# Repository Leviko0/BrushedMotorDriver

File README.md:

# BrushedMotorDriver

This driver board is designed for two 12V brushed motors based on an ESP32 and two DRV8245. It utilizes the NCV68261 for reverse current and reverse polarity protection and for power enable.

## Hardware overview

- **MCU:** ESP32-S3-WROOM-1
- **Motor drivers:** 2x TI DRV8245 (12V brushed DC motor driver)
- **Protection:** NCV68261 for reverse current/polarity protection and power enable, with DRVOFF fault handling
- **Power input:** XT60 connector for a 4S LiPo battery
- **Regulator:** TLV75533 LDO, 3.3V rail for the ESP32
- **Programming/data:** USB-C connector (USB 2.0)

## PCB design

- **4-layer stackup** with dedicated ground and power planes, to separate the ESP32's digital/RF signals from the motor drivers' switching noise
- **Thermal via arrays** under the DRV8245 exposed pads for heat dissipation
- **Ground stitching vias** to keep return paths low-impedance across the board
- **Trace widths scaled by current:** wider power traces for the motor outputs, standard-width traces for signal/logic

Schematic: <br />

<br />

PCB: <br />

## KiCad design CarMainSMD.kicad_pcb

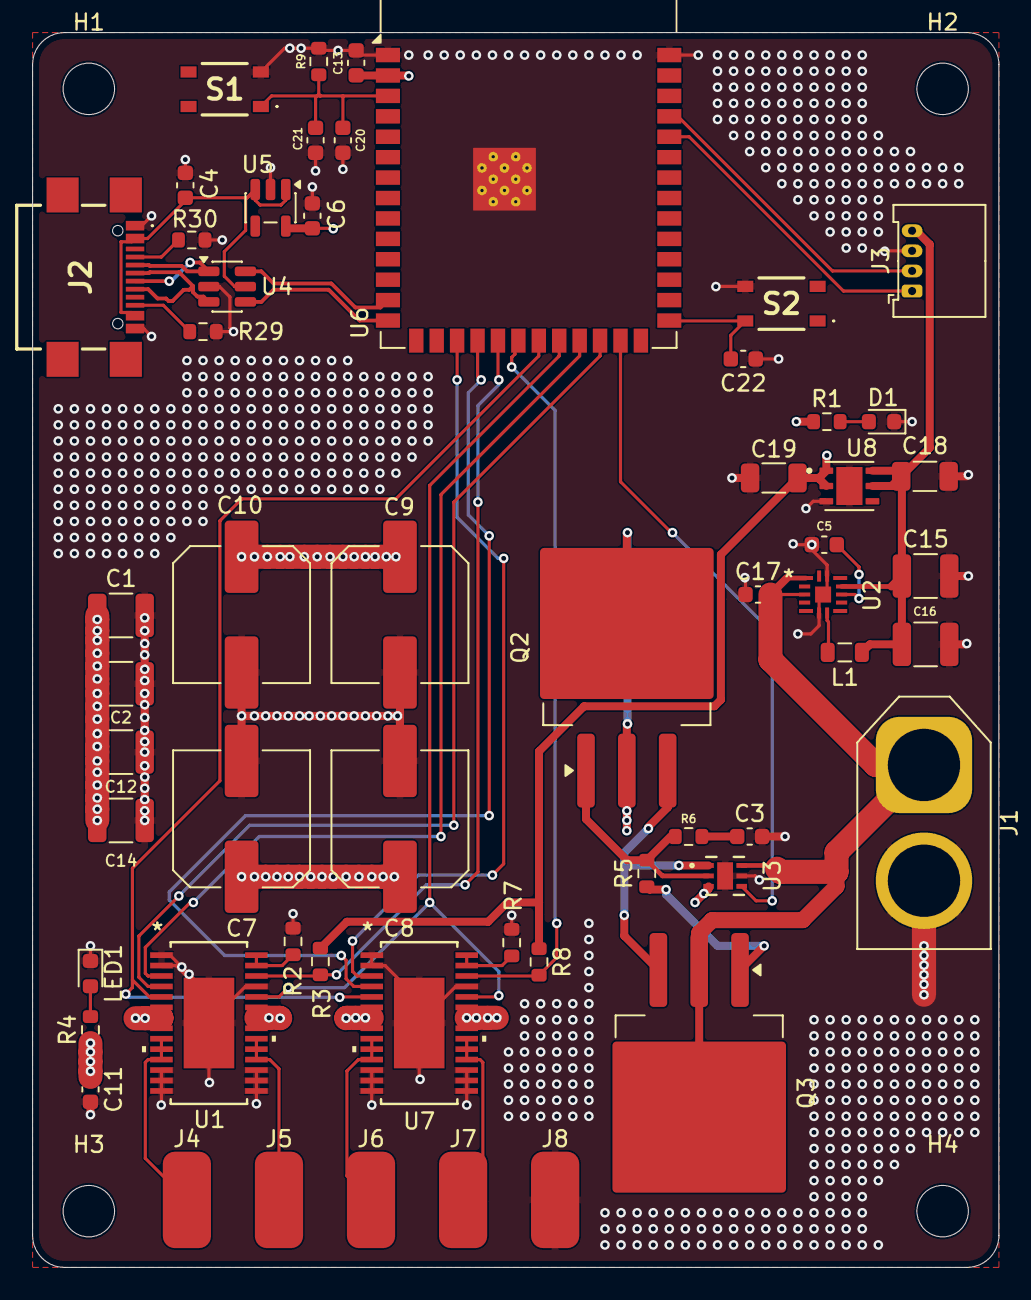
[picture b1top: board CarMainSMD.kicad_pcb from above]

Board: 4 copper layers, 60.1 x 76.8 mm, 60 parts (0 on the bottom side), 39 nets.

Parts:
C1, C2, C12, C14, C15, C16: 22uF; C_1210_3225Metric
C3: 20nF; C_0603_1608Metric
C4, C5, C21: 1uF; C_0603_1608Metric
C6, C13, C17: 4.7uF; C_0603_1608Metric
C7, C8, C9, C10: 220uF; C_Elec_8x10.2
C11, C20, C22: 0.1uF; C_0603_1608Metric
C18, C19: 10uF; C_1206_3216Metric
D1: LED_Small; LED_0603_1608Metric
H1, H2, H3, H4: MountingHole; MountingHole_3.2mm_M3
J1: 4DB-P108-02; AMASS_XT60-F_1x02_P7.20mm_Vertical
J2: USB_C_Receptacle_USB2.0_16P; USB494000A
J3: Conn_01x04_Pin; Molex_PicoBlade_53048-0410_1x04_P1.25mm_Horizontal
J4, J5, J6, J7, J8: Conn_01x01; SolderWirePad_1x01_SMD_3x6mm
L1: 2.2uH; L_0805_2012Metric
LED1: Green; LED_0603_1608Metric
Q2, Q3: NMOS; TO-263-3_TabPin2
R1: 68; R_0603_1608Metric
R2, R7: 8.2k; R_0603_1608Metric
R3, R4, R8, R9: 10k; R_0603_1608Metric
R5, R6: 10; R_0603_1608Metric
R29, R30: 5.1k; R_0603_1608Metric
S1, S2: PTS815SJM250SMTR_LFS; PTS815SJM250SMTRLFS
U1, U7: DRV8245HQPWPRQ1; HTSSOP28_PWP_TEX
U2: LMQ66430MC5RXBRQ1; VQFN-FCRLF14_RXB_TEX
U3: NCV68261MTWAITBG; WDFNW6_511DW_ONS_OSI
U4: USBLC6-2SC6; SOT-23-6
U5: TLV75533PDBV; SOT-23-5
U6: ESP32-S3-WROOM-1
U8: LD39200PU33R; SON95P300X300X100-7N

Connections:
+3V3: C6.1, C13.1, C19.1, R1.1, R3.1, R8.1, U5.5 (OUT), U6.2 (3V3), U8.1 (OUT), U8.2 (SENSE)
+5V: C15.1, C16.1, C18.2, J3.4, L1.1, U2.11 (VOUT/FB), U8.5 (EN), U8.6 (IN)
/AO1: J4.1 (Pin_1_1), U1.9 (OUT1), U1.10 (OUT1), U1.11 (OUT1)
/AO2: J5.1 (Pin_1_1), U1.18 (OUT2), U1.19 (OUT2), U1.20 (OUT2)
/A_DIR: U1.3 (PH/IN2), U6.23 (IO21)
/A_PWM: U1.4 (EN/IN1), U6.24 (IO47)
/BO1: J6.1 (Pin_1_1), U7.9 (OUT1), U7.10 (OUT1), U7.11 (OUT1)
/BO2: J7.1 (Pin_1_1), U7.18 (OUT2), U7.19 (OUT2), U7.20 (OUT2)
/BOOT: C22.2, S2.2 (COM_2), U6.27 (IO0)
/B_DIR: U6.17 (IO9), U7.3 (PH/IN2)
/B_PWM: U6.18 (IO10), U7.4 (EN/IN1)
/D+: J2.A6 (D+), J2.B6 (D+), U4.3 (I/O2)
/D-: J2.A7 (D-), J2.B7 (D-), U4.1 (I/O1)
/DRVOFF: U1.5 (DRVOFF), U6.21 (IO13), U7.5 (DRVOFF)
/EN: U3.4 (EN), U6.25 (IO48)
/EXT_VIN: C17.2, J1.1, Q3.2 (D), U2.1 (EN), U2.3 (VIN), U3.6 (IN)
/NSLEEP: U1.24 (NSLEEP), U6.22 (IO14), U7.24 (NSLEEP)
/RXD: J3.2, U6.37 (TXD0)
/TXD: J3.1, U6.36 (RXD0)
/USB_D+: U4.4 (I/O2), U6.14 (USB_D+)
/USB_D-: U4.6 (I/O1), U6.13 (USB_D-)
/VIN: C1.1, C2.1, C7.1, C8.1, C9.1, C10.1, C11.1, C12.1, C14.1, Q2.2 (D), R4.1, U1.6 (VM), U1.7 (VM), U1.8 (VM), U1.21 (VM), U1.22 (VM), U1.23 (VM), U3.3 (D), U7.6 (VM), U7.7 (VM), U7.8 (VM), U7.21 (VM), U7.22 (VM), U7.23 (VM)
/nFAULT_A: R3.2, U1.26 (NFAULT), U6.19 (IO11)
/nFAULT_B: R8.2, U6.20 (IO12), U7.26 (NFAULT)
/~RESET: C20.2, C21.2, R9.2, S1.1 (COM_1), U6.3 (EN)
GND: C1.2, C2.2, C3.2, C4.2, C5.2, C6.2, C7.2, C8.2, C9.2, C10.2, C11.2, C12.2, C13.2, C14.2, C15.2, C16.2, C17.1, C18.1, C19.2, C20.1, C21.1, C22.1, D1.1 (K), J1.2, J2.A1 (GND), J2.B1 (GND), J3.3, J8.1 (Pin_1_1), LED1.1 (K), R2.1, R7.1, R9.1, R29.2, R30.2, S1.3 (NO_1), S2.4 (NO_2), U1.1 (SR), U1.2 (DIAG), U1.12 (GND), U1.13 (GND), U1.14 (GND), U1.15 (GND), U1.16 (GND), U1.17 (GND), U1.25 (IPROPI), U1.EPAD, U2.6 (PGND), U2.13 (RT), U2.15 (GND/DAP), U3.5 (GND), U3.7 (EPAD), U4.2 (GND), U5.2 (GND), U6.1 (GND), U6.40 (GND), U6.41 (GND), U7.1 (SR), U7.2 (DIAG), U7.12 (GND), U7.13 (GND), U7.14 (GND), U7.15 (GND), U7.16 (GND), U7.17 (GND), U7.25 (IPROPI), U7.EPAD, U8.3 (GND), U8.7 (EXP)
unnamed: C3.1, R6.1
unnamed: D1.2 (A), R1.2
unnamed: J2.A5 (CC1), R30.1
unnamed: J2.B5 (CC2), R29.1
unnamed: LED1.2 (A), R4.2
unnamed: Q2.1 (G), R5.2, R6.2, U3.2 (G)
unnamed: Q2.3 (S), Q3.3 (S), U3.1 (S)
unnamed: Q3.1 (G), R5.1
unnamed: R2.2, U1.27 (MODE), U1.28 (ITRIP)
unnamed: L1.2, U2.7 (SW)
unnamed: C5.1, U2.10 (VCC)
unnamed: C4.1, J2.A4 (VBUS), J2.B4 (VBUS), U4.5 (VBUS), U5.1 (IN), U5.3 (EN)
unnamed: R7.2, U7.27 (MODE), U7.28 (ITRIP)
